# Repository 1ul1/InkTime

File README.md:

# InkTime
## Block Diagram

If GitHub does not render Mermaid, use this ASCII version instead:

# Block Diagram

### Summary

The nRF52840 is the main controller of the board.
Power comes from USB-C and the Li-Po battery through the BQ25180 charger and the RT6160A DC/DC regulator. The MCU talks over I2C with the BMA421 IMU, MAX17048 fuel gauge, and DRV2605 haptic driver. It also controls the E-Paper display through SPI and extra control lines, reads the buttons, and exposes SWD for programming and debug.

### Overview
```
USB-C -----> nRF52840 <-----> BMA421 IMU
  |             |               (I2C)
  |             |
  |             +-------------> Buttons
  |             |
  |             +-------------> SWD Header
  |             |
  |             +-------------> E-Paper Display
  |                    (SPI + control)
  |
  +-----> BQ25180 Charger -----> Li-Po Battery
                 |
                 +-----> RT6160A DC/DC -----> 3V3 
                                          |-> nRF52840
                                          |-> MAX17048 Fuel Gauge
                                          |-> DRV2605 Haptic Driver
                                          |-> E-Paper Drive Circuit
```

## Bill of Materials (BOM)

The table below lists the main parts used in the project.  
For standard passives (0201 / 0402 capacitors and resistors), the exact values and designators are already included in `BOM.csv`.  
JLC links below are **search links**, so you can quickly find the matching part on JLC Parts.

| Designators | Qty | Part / Function | Manufacturer | MPN | Package / Notes | JLC Parts | Datasheet |
|---|---:|---|---|---|---|---|---|
| U1 | 1 | Main MCU | Nordic Semiconductor | nRF52840 | AQFN-73 / 7x7 mm | [JLC Search](https://jlcpcb.com/parts/componentSearch?searchTxt=nRF52840) | [Datasheet](https://docs.nordicsemi.com/bundle/ps_nrf52840/page/keyfeatures_html5.html) |
| IC1 | 1 | Li-Po charger | Texas Instruments | BQ25180YBGR | DSBGA-8 | [JLC Search](https://jlcpcb.com/parts/componentSearch?searchTxt=BQ25180YBGR) | [Datasheet](https://www.ti.com/lit/gpn/BQ25180) |
| IC9 | 1 | Buck-boost regulator | Richtek | RT6160AWSC | WL-CSP-15 | [JLC Search](https://jlcpcb.com/parts/componentSearch?searchTxt=RT6160AWSC) | [Datasheet](https://www.mouser.com/datasheet/2/1458/DS6160A_02-3104604.pdf) |
| IC3 | 1 | IMU / accelerometer | Bosch Sensortec | BMA423 | LGA-12 | [JLC Search](https://jlcpcb.com/parts/componentSearch?searchTxt=BMA423) | [Datasheet](https://watchy.sqfmi.com/assets/files/BST-BMA423-DS000-1509600-950150f51058597a6234dd3eaafbb1f0.pdf) |
| U3 | 1 | Fuel gauge | Analog Devices / Maxim | MAX17048G+T10 | 9-bump UCSP | [JLC Search](https://jlcpcb.com/parts/componentSearch?searchTxt=MAX17048G%2BT10) | [Datasheet](https://www.analog.com/media/en/technical-documentation/data-sheets/max17048-max17049.pdf) |
| IC2 | 1 | Haptic driver | Texas Instruments | DRV2605YZFR | DSBGA-9 | [JLC Search](https://jlcpcb.com/parts/componentSearch?searchTxt=DRV2605YZFR) | [Datasheet](https://www.ti.com/lit/ds/symlink/drv2605.pdf) |
| ANT1 | 1 | 2.4 GHz chip antenna | Johanson Technology | 2450AT18B100E | Ceramic antenna | [JLC Search](https://jlcpcb.com/parts/componentSearch?searchTxt=2450AT18B100E) | [Datasheet](https://www.johansontechnology.com/docs/1187/2450AT18B100_X8XXogU.pdf) |
| J1 | 1 | E-paper FPC connector | Molex | 503480-2400 | 24-pin, 0.5 mm pitch | [JLC Search](https://jlcpcb.com/parts/componentSearch?searchTxt=503480-2400) | [Datasheet](https://www.molex.com/en-us/products/part-detail/5034802400) |
| J4 | 1 | USB-C connector | Kinghelm | KH-TYPE-C-16P | USB Type-C, SMT | [JLC Search](https://jlcpcb.com/parts/componentSearch?searchTxt=KH-TYPE-C-16P) | [Datasheet](https://datasheet.lcsc.com/lcsc/2404191039_Shenzhen-Kinghelm-Elec-KH-TYPE-C-16P_C709357.pdf) |
| J2 | 1 | SWD programming connector | Tag-Connect | TC2030-IDC | 6-pin cable / debug | [JLC Search](https://jlcpcb.com/parts/componentSearch?searchTxt=TC2030-IDC) | [Datasheet](https://www.tag-connect.com/wp-content/uploads/bsk-pdf-manager/2019/12/TC2030-IDC-Datasheet-Rev-B.pdf) |
| D3 | 1 | USB ESD protection | STMicroelectronics | USBLC6-2SC6Y | SOT-23-6 | [JLC Search](https://jlcpcb.com/parts/componentSearch?searchTxt=USBLC6-2SC6Y) | [Datasheet](https://www.st.com/resource/en/datasheet/usblc6-2sc6y.pdf) |
| D2, D4, D5 | 3 | Schottky diode | onsemi | MBR0530 | SOD-123 | [JLC Search](https://jlcpcb.com/parts/componentSearch?searchTxt=MBR0530) | [Datasheet](https://www.onsemi.com/pdf/datasheet/mbr0530t1-d.pdf) |
| Q3 | 1 | N-MOSFET | Vishay | SI1308EDL-T1-GE3 | SC-70 | [JLC Search](https://jlcpcb.com/parts/componentSearch?searchTxt=SI1308EDL-T1-GE3) | [Datasheet](https://www.vishay.com/docs/63399/si1308edl.pdf) |
| Q1 | 1 | P-MOSFET | Diodes Inc. / equivalent | DMG2305UX-7 | SOT-23 | [JLC Search](https://jlcpcb.com/parts/componentSearch?searchTxt=DMG2305UX-7) | [Datasheet](https://www.diodes.com/assets/Datasheets/DMG2305UX.pdf) |
| L7 | 1 | Power inductor | TDK | MLP2016SR47MT0S1 | 0.47 uH | [JLC Search](https://jlcpcb.com/parts/componentSearch?searchTxt=MLP2016SR47MT0S1) | [Datasheet](https://product.tdk.com/system/files/dam/doc/product/inductor/inductor/smd/catalog/inductor_commercial_multilayer_mlp2016_en.pdf) |
| L5 | 1 | Inductor | Generic / selected by value | 68uH | E-paper drive | [JLC Search](https://jlcpcb.com/parts/componentSearch?searchTxt=68uH) | - |
| L2 | 1 | Inductor | Generic / selected by value | 10uH | Power stage | [JLC Search](https://jlcpcb.com/parts/componentSearch?searchTxt=10uH) | - |
| L1 | 1 | RF inductor | Generic / selected by value | 3.9nH | RF matching | [JLC Search](https://jlcpcb.com/parts/componentSearch?searchTxt=3.9nH) | - |
| L3 | 1 | RF inductor | Generic / selected by value | 15nH | RF matching | [JLC Search](https://jlcpcb.com/parts/componentSearch?searchTxt=15nH) | - |
| X1 | 1 | High-frequency crystal | Generic / selected by value | 32MHz | 2016 package | [JLC Search](https://jlcpcb.com/parts/componentSearch?searchTxt=32MHz) | - |
| X2 | 1 | RTC crystal | Generic / selected by value | 32.768kHz | 3215 package | [JLC Search](https://jlcpcb.com/parts/componentSearch?searchTxt=32.768kHz) | - |
| SW_UP, SW_ENT, SW_DN | 3 | Push buttons | Panasonic | EVP-AKE31A | SMD tactile switch | [JLC Search](https://jlcpcb.com/parts/componentSearch?searchTxt=EVP-AKE31A) | [Datasheet](https://industrial.panasonic.com/cdbs/www-data/pdf/ABV0000/ABV0000C90.pdf) |
| TP_3.3V, TP_BAT_GND, TP_GND, TP_ON, TP_OP, TP_RESET, TP_SCL, TP_SDA, TP_SWDCLK, TP_SWDIO, TP_SWO, TP_VBAT | 12 | Test pads | Generic | TP20R | Debug / measurement | [JLC Search](https://jlcpcb.com/parts/componentSearch?searchTxt=test%20pad) | - |

### Standard passives

The board also uses standard SMD resistors and capacitors:

- **All resistors:** 0201
- **Capacitors <= 100 nF:** 0201
- **Capacitors > 100 nF:** 0402
- Exceptions are used only where the schematic explicitly asks for another case

Examples from this design:
- 12 pF, 1 pF, 100 nF, 47 nF, 820 pF, 100 pF capacitors
- 1 uF, 4.7 uF, 10 uF, 22 uF capacitors
- 0R, 2.2R, 470 mR, 3.3 kR, 5.1 kR, 10 kR resistors

For these passives, the exact reference designators, values, and package choices are already listed in `BOM.csv`.

## Hardware Overview

[SCHEMATIC](./Hardware/Schematic.pdf)

### MCU: nRF52840
Central processor managing all peripherals and communication interfaces (GPIO, I2C, SPI, USB).

### Power section
Li‑Po charger (BQ25180) and DC/DC regulator (RT6160A) handle battery charging and generate system voltage rails.

### IMU
BMA421 accelerometer on the I2C bus providing motion data and interrupt outputs.

### USB‑C and ESD protection
USB‑C port supplies power and data, with ESD components protecting the USB lines.

### E‑Paper display
SPI‑driven display connected via FPC, supported by dedicated driving circuitry for panel voltages.

### Fuel gauge
MAX17048 on I2C measuring battery voltage and state‑of‑charge.

### Buttons
Three user buttons (UP, ENTER, DOWN) connected to MCU GPIO pins.

### Haptic driver
DRV2605 (I2C) controlling a vibration motor for tactile feedback.

### SWD debug header
Provides SWDIO, SWDCLK, reset, power, and ground for programming and debugging.

### Block connections
Power flows from USB/battery through charger and regulators; I2C links IMU, fuel gauge, and haptics; SPI and control lines drive the display; GPIO handles buttons and interrupts.

## Central processor - nRF52840

### Short summary
The nRF52840 coordinates the entire system—power, sensors, display, buttons, and haptics—acting as the central controller for all board functions.

### Pins

the nRF52840 uses:
- **native USB pins** for USB,
- **one shared I2C bus** for low-speed peripheral chips,
- **SPI + control pins** for the e-paper display,
- **GPIO inputs** for buttons,
- **interrupt pins** for IMU, battery, and power events,
- and **SWD pins** for debug.

### Why these choices make sense

- **USB** is connected to the nRF52840 native USB pins, so firmware upload and USB communication are direct and simple.
- **I2C** is used for support chips like the charger, IMU, fuel gauge, and haptic driver because these parts only need low-speed control.
- **SPI** is used for the e-paper display because it is better for sending display data.
- **Interrupt lines** such as **ALERT**, **PMIC_INT**, **IMU_INT1**, and **IMU_INT2** help the MCU wake up only when needed, which is better for low power.
- **Buttons** are on simple GPIO pins because they only need digital input reads.
- **SWDIO**, **SWDCLK**, and **RESET** are broken out for easy programming and debugging during bring-up.

## End Result

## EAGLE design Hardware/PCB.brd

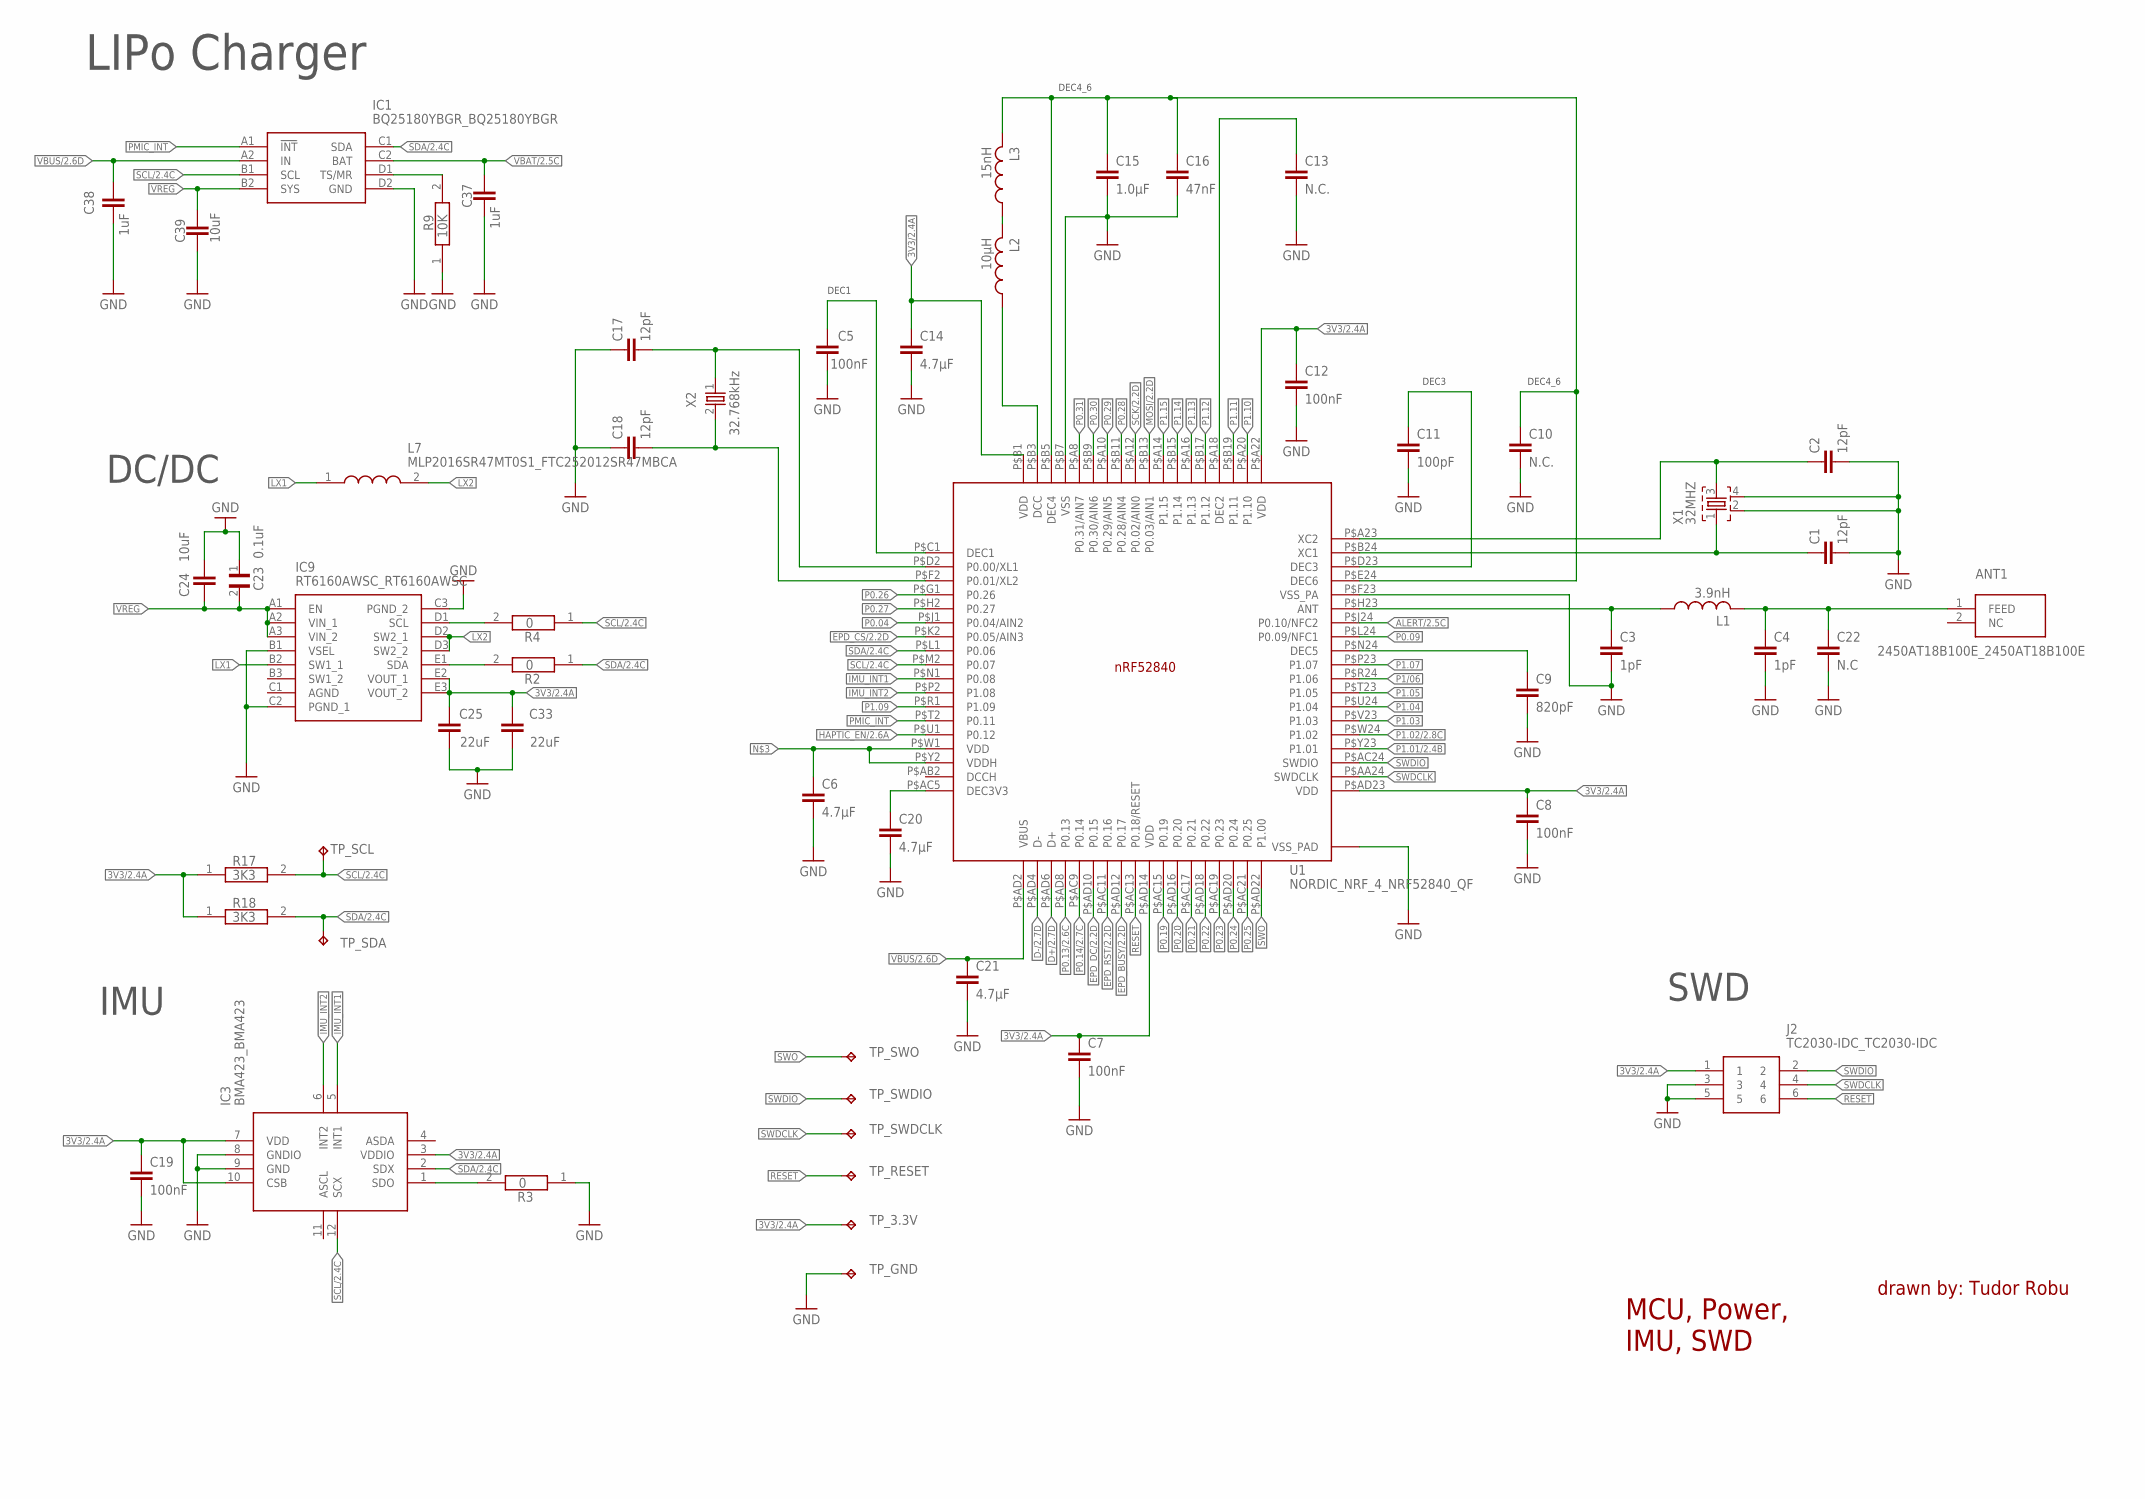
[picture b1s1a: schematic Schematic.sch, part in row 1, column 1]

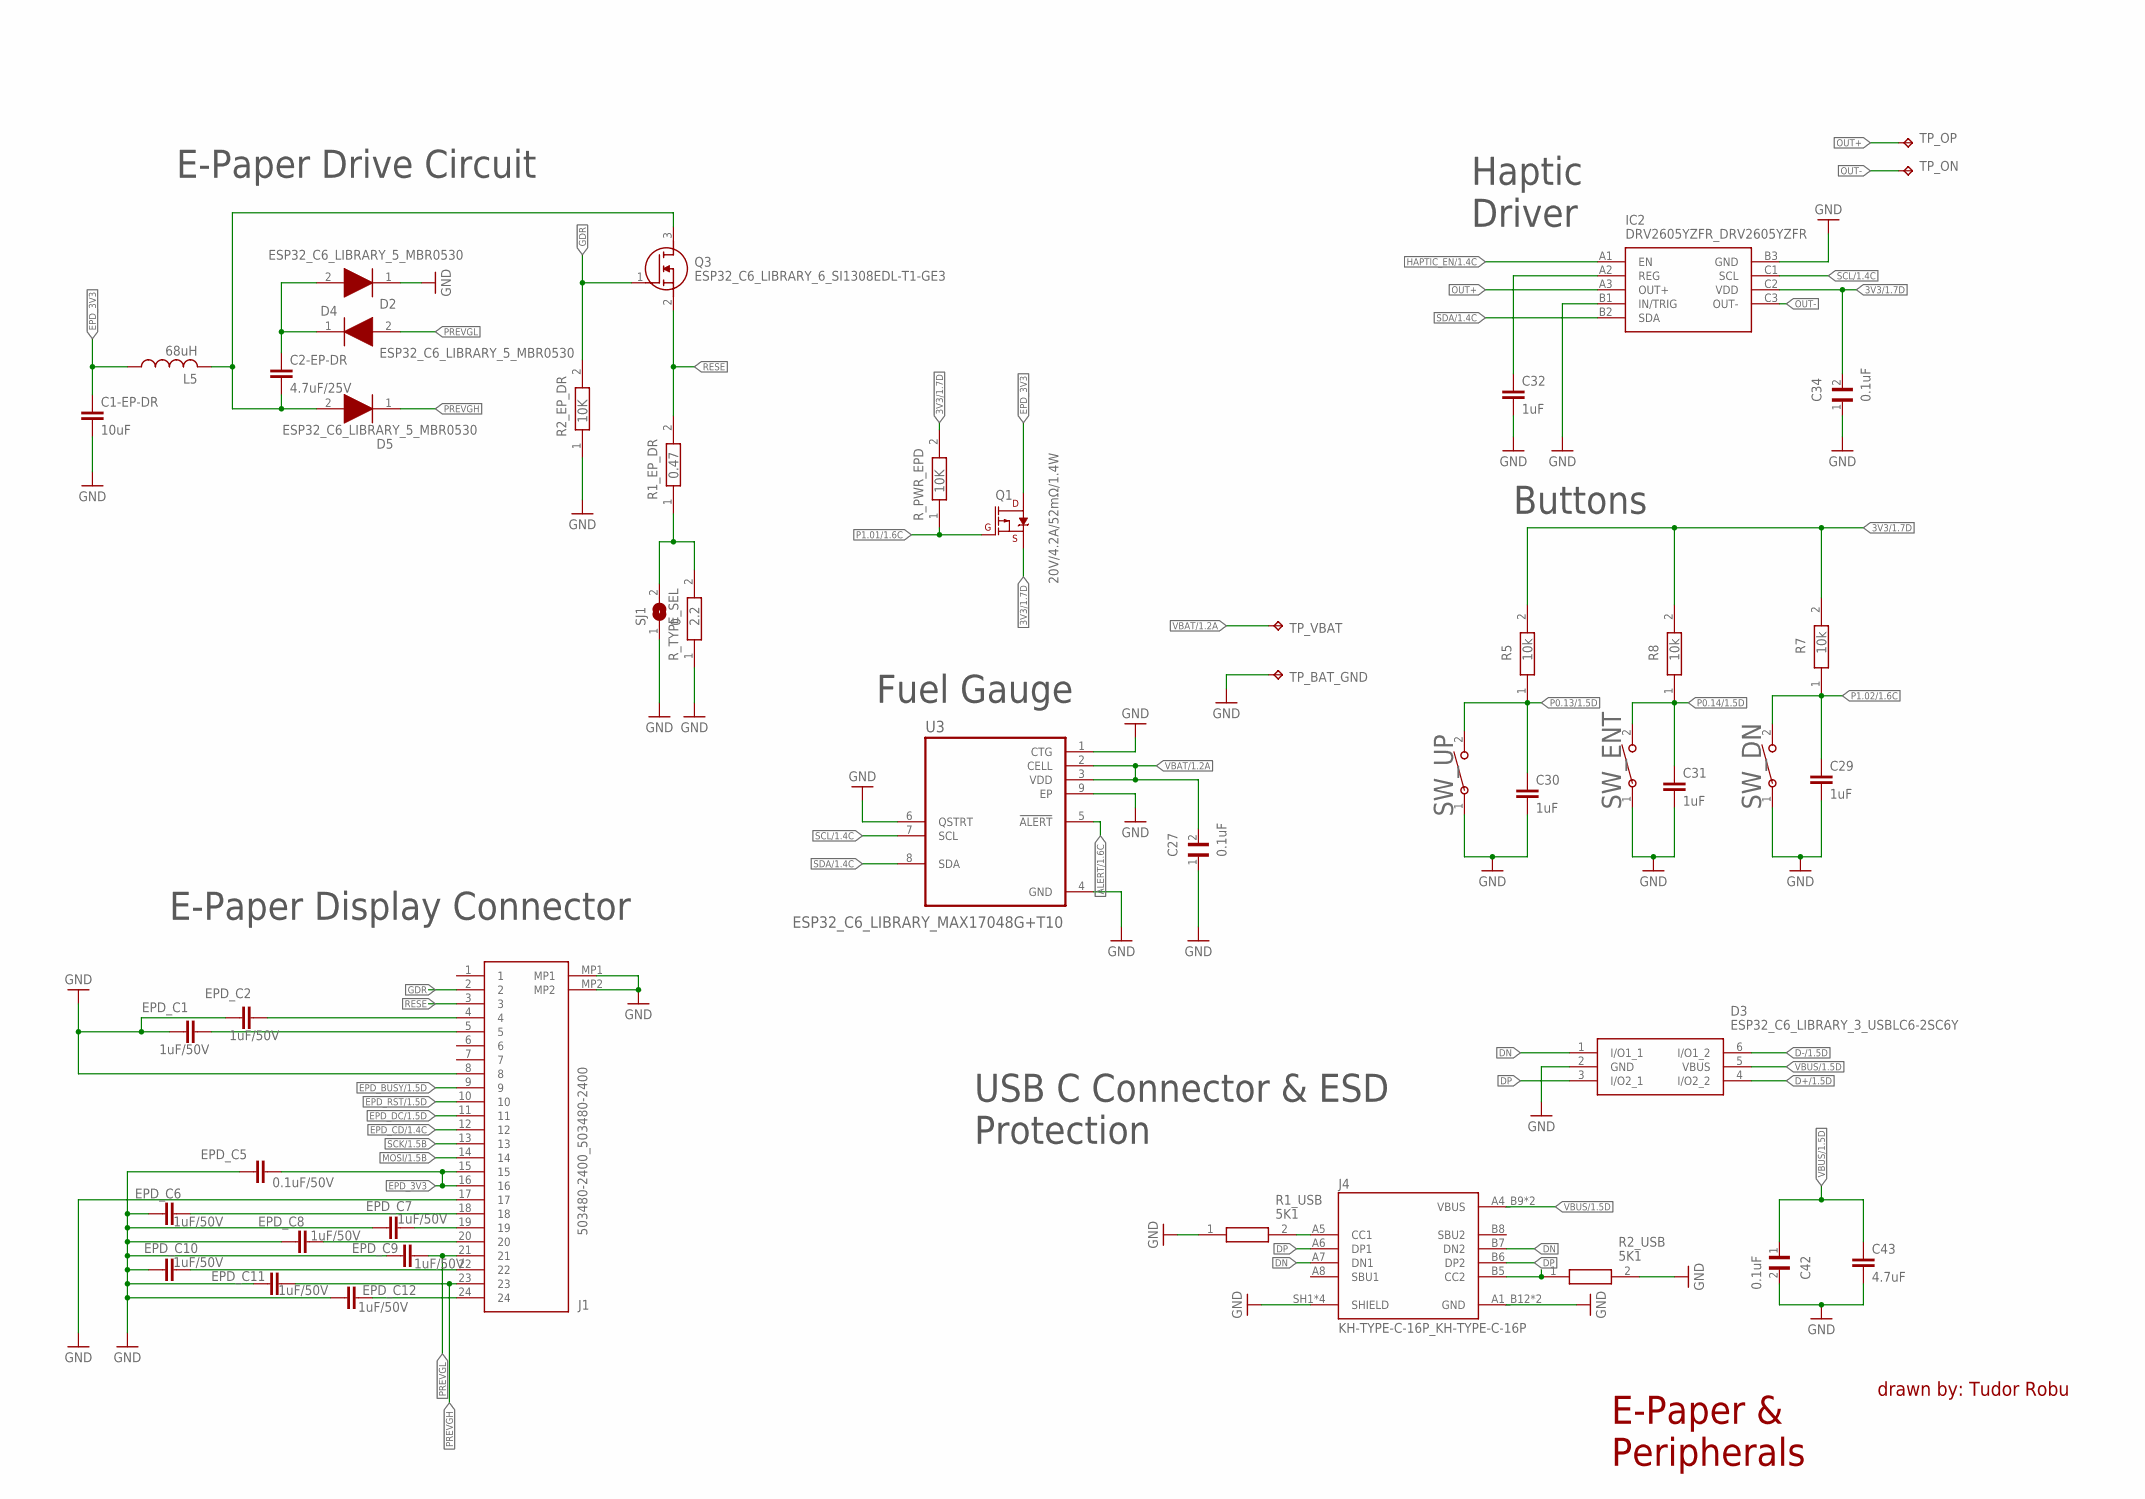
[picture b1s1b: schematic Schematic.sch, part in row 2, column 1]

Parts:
ANT1: 2450AT18B100E_2450AT18B100E; 2450AT18B100E_ANTC3216X140N
C1, C2, C17, C18: 12pF; NORDIC_NRF_3_RESC0201_L
C1-EP-DR, C24, C39: 10uF; PERFECT_0402_0402
C2-EP-DR: 4.7uF/25V; PERFECT_0402_0402
C3, C4: 1pF; NORDIC_NRF_3_RESC0201_L
C5, C8, C12, C19: 100nF; NORDIC_NRF_3_RESC0201_L
C6, C14, C20, C21: 4.7µF; PERFECT_0402_0402
C7: 100nF; PERFECT_0402_0402
C9: 820pF; NORDIC_NRF_3_RESC0201_L
C10: N.C.; NORDIC_NRF_3_RESC0201_L
C11: 100pF; NORDIC_NRF_3_RESC0201_L
C13: N.C.; PERFECT_0402_0402
C15: 1.0µF; PERFECT_0402_0402
C16: 47nF; NORDIC_NRF_3_RESC0201_L
C22: N.C; NORDIC_NRF_3_RESC0201_L
C23, C27, C34, C42: 0.1uF; GRM011R60J152KE01L_2_CAPC0201X13N
C25, C33: 22uF; PERFECT_0402_0402
C29, C30, C31, C32, C37, C38: 1uF; PERFECT_0402_0402
C43: 4.7uF; PERFECT_0402_0402
D2, D4, D5: ESP32_C6_LIBRARY_5_MBR0530; ESP32_C6_LIBRARY_5_SOD3716X135N
D3: ESP32_C6_LIBRARY_3_USBLC6-2SC6Y; ESP32_C6_LIBRARY_3_SOT95P280X145-6N
EPD_C1, EPD_C2, EPD_C6, EPD_C7, EPD_C8, EPD_C9, EPD_C10, EPD_C11, EPD_C12: 1uF/50V; PERFECT_0402_0402
EPD_C5: 0.1uF/50V; NORDIC_NRF_3_RESC0201_L
IC1: BQ25180YBGR_BQ25180YBGR; BQ25180YBGR_BGA8C40P2X4_100X155X50
IC2: DRV2605YZFR_DRV2605YZFR; DRV2605YZFR_BGA9C50P3X3_144X144X62
IC3: BMA423_BMA423
IC9: RT6160AWSC_RT6160AWSC; RT6160AWSC_BGA15C40P3X5_140X230X60
J1: 503480-2400_503480-2400; 503480-2400_5034802400
J2: TC2030-IDC_TC2030-IDC; TC2030-IDC_TC2030IDC
J4: KH-TYPE-C-16P_KH-TYPE-C-16P; KH-TYPE-C-16P_KINGHELM_KH-TYPE-C-16P
L1: 3.9nH; NORDIC_NRF_2_RESC0402_L
L2: 10µH; NORDIC_NRF_2_RESC0402_L
L3: 15nH; NORDIC_NRF_2_RESC0402_L
L5: 68uH; NORDIC_NRF_2_RESC0402_L
L7: MLP2016SR47MT0S1_FTC252012SR47MBCA; MLP2016SR47MT0S1_INDC2016X100N
Q1: 20V/4.2A/52mΩ/1.4W; ESP32_C6_LIBRARY_4_ESP32_C6_LIBRARY_4_ESP32_C6_LIBRARY_4_ES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
Q3: ESP32_C6_LIBRARY_6_SI1308EDL-T1-GE3; ESP32_C6_LIBRARY_6_SOT65P210X110-3N
R1_EP_DR: 0.47; CPF0201D7K68C1_0201
R1_USB, R2_USB: 5K1; CPF0201D7K68C1_0201
R2, R3, R4: 0; ERA-1AEB3401C_0201
R2_EP_DR, R9: 10K; CPF0201D7K68C1_0201
R5, R7, R8: 10k; CPF0201D7K68C1_0201
R17, R18: 3K3; ERA-1AEB3401C_0201
R_PWR_EPD: 10K; CPF0201D7K68C1_0201
R_TYPE_SEL: 2.2; CPF0201D7K68C1_0201
SJ1: 0; ESP32_C6_LIBRARY_7_JUMPER_SJ
SW_DN: 2025-10-22_07-23-44_LIBRARY_EVP-AKE31ASW_EVP-AKE3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; 2025-10-22_07-23-44_LIBRARY_SW_EVP-AKE31A_PAN
SW_ENT: 2025-10-22_07-23-44_LIBRARY_EVP-AKE31ASW_EVP-AKE3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; 2025-10-22_07-23-44_LIBRARY_SW_EVP-AKE31A_PAN
SW_UP: 2025-10-22_07-23-44_LIBRARY_EVP-AKE31ASW_EVP-AKE3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; 2025-10-22_07-23-44_LIBRARY_SW_EVP-AKE31A_PAN
TP_3.3V: HECTOR_WATCH_1_TPTP20R; HECTOR_WATCH_1_TP20R
TP_BAT_GND: HECTOR_WATCH_1_TPTP20R; HECTOR_WATCH_1_TP20R
TP_GND: HECTOR_WATCH_1_TPTP20R; HECTOR_WATCH_1_TP20R
TP_ON: HECTOR_WATCH_1_TPTP20R; HECTOR_WATCH_1_TP20R
TP_OP: HECTOR_WATCH_1_TPTP20R; HECTOR_WATCH_1_TP20R
TP_RESET: HECTOR_WATCH_1_TPTP20R; HECTOR_WATCH_1_TP20R
TP_SCL: HECTOR_WATCH_1_TPTP20R; HECTOR_WATCH_1_TP20R
TP_SDA: HECTOR_WATCH_1_TPTP20R; HECTOR_WATCH_1_TP20R
TP_SWDCLK: HECTOR_WATCH_1_TPTP20R; HECTOR_WATCH_1_TP20R
TP_SWDIO: HECTOR_WATCH_1_TPTP20R; HECTOR_WATCH_1_TP20R
TP_SWO: HECTOR_WATCH_1_TPTP20R; HECTOR_WATCH_1_TP20R
TP_VBAT: HECTOR_WATCH_1_TPTP20R; HECTOR_WATCH_1_TP20R
U1: NORDIC_NRF_4_NRF52840_QF; NORDIC_NRF_4_AQFN50P700X700X85_HS-74N
U3: ESP32_C6_LIBRARY_MAX17048G+T10; ESP32_C6_LIBRARY_SON50P200X200X80-9N
X1: 32MHZ; NORDIC_NRF_BT-XTAL_2016_N
X2: 32.768kHz; NORDIC_NRF_1_XTAL_3215_N

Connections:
3V3/1.7D: C34.2, IC2.C2 (VDD), Q1.2 (S), R5.2, R7.2, R8.2, R_PWR_EPD.2
3V3/2.4A: C7.1, C8.1, C12.1, C14.1, C19.1, C25.2, C33.2, IC3.3 (VDDIO), IC3.7 (VDD), IC3.10 (CSB), IC9.E2 (VOUT_1), IC9.E3 (VOUT_2), J2.1, R17.1, R18.1, TP_3.3V.TP, U1.P$A22 (VDD), U1.P$AD14 (VDD), U1.P$AD23 (VDD), U1.P$B1 (VDD)
ALERT/1.6C: U3.5 (!ALERT)
ALERT/2.5C: U1.P$J24 (P0.10/NFC2)
D+/1.5D: D3.4 (I/O2_2)
D+/2.7D: U1.P$AD6 (D+)
D-/1.5D: D3.6 (I/O1_2)
D-/2.7D: U1.P$AD4 (D-)
DN: D3.1 (I/O1_1), J4.A7 (DN1), J4.B7 (DN2)
DP: D3.3 (I/O2_1), J4.A6 (DP1), J4.B6 (DP2)
EPD_3V3: C1-EP-DR.1, EPD_C5.2, J1.15, J1.16, L5.1, Q1.3 (D)
EPD_BUSY/1.5D: J1.9
EPD_BUSY/2.2D: U1.P$AC11 (P0.16)
EPD_CD/1.4C: J1.12
EPD_CS/2.2D: U1.P$K2 (P0.05/AIN3)
EPD_DC/1.5D: J1.11
EPD_DC/2.2D: U1.P$AD10 (P0.15)
EPD_RST/1.5D: J1.10
EPD_RST/2.2D: U1.P$AD12 (P0.17)
GDR: J1.2, Q3.1 (G), R2_EP_DR.2
GND: C1.2, C1-EP-DR.2, C2.2, C3.2, C4.2, C5.1, C6.2, C7.2, C8.2, C9.2, C10.2, C11.2, C12.2, C13.2, C14.2, C15.2, C16.2, C17.1, C18.1, C19.2, C20.2, C21.2, C22.2, C23.1, C24.2, C25.1, C27.1, C29.2, C30.2, C31.2, C32.2, C33.1, C34.1, C37.2, C38.2, C39.2, C42.2, C43.2, D3.2 (GND), D4.1 (K), EPD_C1.1, EPD_C2.1, EPD_C5.1, EPD_C6.1, EPD_C7.1, EPD_C8.1, EPD_C9.1, EPD_C10.1, EPD_C11.1, EPD_C12.1, IC1.D2 (GND), IC2.B1 (IN/TRIG), IC2.B3 (GND), IC3.8 (GNDIO), IC3.9 (GND), IC9.B1 (VSEL), IC9.C2 (PGND_1), IC9.C3 (PGND_2), J1.8, J1.17, J1.MP1, J1.MP2, J2.3, J2.5, J4.A1_B12 (GND), J4.A12_B1 (GND), J4.SH1 (SHIELD), J4.SH2 (SHIELD), J4.SH3 (SHIELD), J4.SH4 (SHIELD), R1_USB.1, R2_EP_DR.1, R2_USB.2, R3.1, R9.1, R_TYPE_SEL.1, SJ1.1, SW_DN.1, SW_ENT.1, SW_UP.1, TP_BAT_GND.TP, TP_GND.TP, U1.P$74 (VSS_PAD), U1.P$75 (VSS_PAD), U1.P$76 (VSS_PAD), U1.P$77 (VSS_PAD), U1.P$78 (VSS_PAD), U1.P$79 (VSS_PAD), U1.P$80 (VSS_PAD), U1.P$81 (VSS_PAD), U1.P$82 (VSS_PAD), U1.P$83 (VSS_PAD), U1.P$84 (VSS_PAD), U1.P$85 (VSS_PAD), U1.P$86 (VSS_PAD), U1.P$87 (VSS_PAD), U1.P$88 (VSS_PAD), U1.P$89 (VSS_PAD), U1.P$90 (VSS_PAD), U1.P$B7 (VSS), U1.P$F23 (VSS_PA), U3.1 (CTG), U3.4 (GND), U3.6 (QSTRT), U3.9 (EP), X1.2, X1.4
HAPTIC_EN/1.4C: IC2.A1 (EN)
HAPTIC_EN/2.6A: U1.P$U1 (P0.12)
IMU_INT1: IC3.5 (INT1), U1.P$N1 (P0.08)
IMU_INT2: IC3.6 (INT2), U1.P$P2 (P1.08)
LX1: IC9.B2 (SW1_1), L7.1
LX2: IC9.D2 (SW2_1), IC9.D3 (SW2_2), L7.2
MOSI/1.5B: J1.14
MOSI/2.2D: U1.P$B13 (P0.03/AIN1)
unnamed: IC3.1 (SDO), R3.2
unnamed: C20.1, U1.P$AC5 (DEC3V3)
unnamed: C6.1, U1.P$W1 (VDD), U1.P$Y2 (VDDH)
unnamed: C18.2, U1.P$F2 (P0.01/XL2), X2.2
unnamed: C17.2, U1.P$D2 (P0.00/XL1), X2.1
unnamed: C5.2, U1.P$C1 (DEC1)
unnamed: L2.2, L3.1
unnamed: IC1.D1 (TS/MR), R9.2
unnamed: IC9.D1 (SCL), R4.2
unnamed: IC9.E1 (SDA), R2.2
unnamed: L2.1, U1.P$B3 (DCC)
unnamed: C3.1, L1.1, U1.P$H23 (ANT)
unnamed: C13.1, U1.P$A18 (DEC2)
unnamed: C10.1, C15.1, C16.1, L3.2, U1.P$B5 (DEC4), U1.P$E24 (DEC6)
unnamed: C9.1, U1.P$N24 (DEC5)
unnamed: C1.1, U1.P$B24 (XC1), X1.1
unnamed: C11.1, U1.P$D23 (DEC3)
unnamed: C2.1, U1.P$A23 (XC2), X1.3
unnamed: ANT1.1 (FEED), C4.1, C22.1, L1.2
unnamed: J4.A5 (CC1), R1_USB.2
unnamed: C2-EP-DR.2, D5.2 (A), L5.2, Q3.3 (D)
unnamed: C2-EP-DR.1, D2.1 (K), D4.2 (A)
unnamed: C32.1, IC2.A2 (REG)
unnamed: R1_EP_DR.1, R_TYPE_SEL.2, SJ1.2
unnamed: EPD_C2.2, J1.4
unnamed: EPD_C1.2, J1.5
unnamed: J4.B5 (CC2), R2_USB.1
unnamed: EPD_C12.2, J1.24
unnamed: EPD_C10.2, J1.22
unnamed: EPD_C8.2, J1.20
unnamed: EPD_C7.2, J1.19
unnamed: EPD_C6.2, J1.18
OUT+: IC2.A3 (OUT+), TP_OP.TP
OUT-: IC2.C3 (OUT-), TP_ON.TP
P0.04: U1.P$J1 (P0.04/AIN2)
P0.09: U1.P$L24 (P0.09/NFC1)
P0.13/1.5D: C30.1, R5.1, SW_UP.2
P0.13/2.6C: U1.P$AD8 (P0.13)
P0.14/1.5D: C31.1, R8.1, SW_ENT.2
P0.14/2.7C: U1.P$AC9 (P0.14)
P0.19: U1.P$AC15 (P0.19)
P0.20: U1.P$AD16 (P0.20)
P0.21: U1.P$AC17 (P0.21)
P0.22: U1.P$AD18 (P0.22)
P0.23: U1.P$AC19 (P0.23)
P0.24: U1.P$AD20 (P0.24)
P0.25: U1.P$AC21 (P0.25)
P0.26: U1.P$G1 (P0.26)
P0.27: U1.P$H2 (P0.27)
P0.28: U1.P$B11 (P0.28/AIN4)
P0.29: U1.P$A10 (P0.29/AIN5)
P0.30: U1.P$B9 (P0.30/AIN6)
P0.31: U1.P$A8 (P0.31/AIN7)
P1.01/1.6C: Q1.1 (G), R_PWR_EPD.1
P1.01/2.4B: U1.P$Y23 (P1.01)
P1.02/1.6C: C29.1, R7.1, SW_DN.2
P1.02/2.8C: U1.P$W24 (P1.02)
P1.03: U1.P$V23 (P1.03)
P1.04: U1.P$U24 (P1.04)
P1.05: U1.P$T23 (P1.05)
P1.07: U1.P$P23 (P1.07)
P1.09: U1.P$R1 (P1.09)
P1.10: U1.P$A20 (P1.10)
P1.11: U1.P$B19 (P1.11)
P1.12: U1.P$B17 (P1.12)
P1.13: U1.P$A16 (P1.13)
P1.14: U1.P$B15 (P1.14)
P1.15: U1.P$A14 (P1.15)
P1/06: U1.P$R24 (P1.06)
PMIC_INT: IC1.A1 (!INT), U1.P$T2 (P0.11)
PREVGH: D5.1 (K), EPD_C11.2, J1.23
PREVGL: D2.2 (A), EPD_C9.2, J1.21
RESE: J1.3, Q3.2 (S), R1_EP_DR.2
RESET: J2.6, TP_RESET.TP, U1.P$AC13 (P0.18/RESET)
SCK/1.5B: J1.13
SCK/2.2D: U1.P$A12 (P0.02/AIN0)
SCL/1.4C: IC2.C1 (SCL), U3.7 (SCL)
SCL/2.4C: IC1.B1 (SCL), IC3.12 (SCX), R4.1, R17.2, TP_SCL.TP, U1.P$M2 (P0.07)
SDA/1.4C: IC2.B2 (SDA), U3.8 (SDA)
SDA/2.4C: IC1.C1 (SDA), IC3.2 (SDX), R2.1, R18.2, TP_SDA.TP, U1.P$L1 (P0.06)
SWDCLK: J2.4, TP_SWDCLK.TP, U1.P$AA24 (SWDCLK)
SWDIO: J2.2, TP_SWDIO.TP, U1.P$AC24 (SWDIO)
SWO: TP_SWO.TP, U1.P$AD22 (P1.00)
VBAT/1.2A: C27.2, TP_VBAT.TP, U3.2 (CELL), U3.3 (VDD)
VBAT/2.5C: C37.1, IC1.C2 (BAT)
VBUS/1.5D: C42.1, C43.1, D3.5 (VBUS), J4.A4_B9 (VBUS), J4.A9_B4 (VBUS)
VBUS/2.6D: C21.1, C38.1, IC1.A2 (IN), U1.P$AD2 (VBUS)
VREG: C23.2, C24.1, C39.1, IC1.B2 (SYS), IC9.A1 (EN), IC9.A2 (VIN_1), IC9.A3 (VIN_2)

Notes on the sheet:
SWD
IMU
DEC1
DEC4_6
DEC3
LIPo Charger
DC/DC
E-Paper Drive Circuit
E-Paper Display Connector
Fuel Gauge
Buttons
Haptic Driver
USB C Connector & ESD Protection
MCU, Power, IMU, SWD
drawn by: Tudor Robu
E-Paper & Peripherals

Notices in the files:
parts and their libraries:
COPYRIGHT: Copyright (C) 2025 Ultra Librarian. All rights reserved.
